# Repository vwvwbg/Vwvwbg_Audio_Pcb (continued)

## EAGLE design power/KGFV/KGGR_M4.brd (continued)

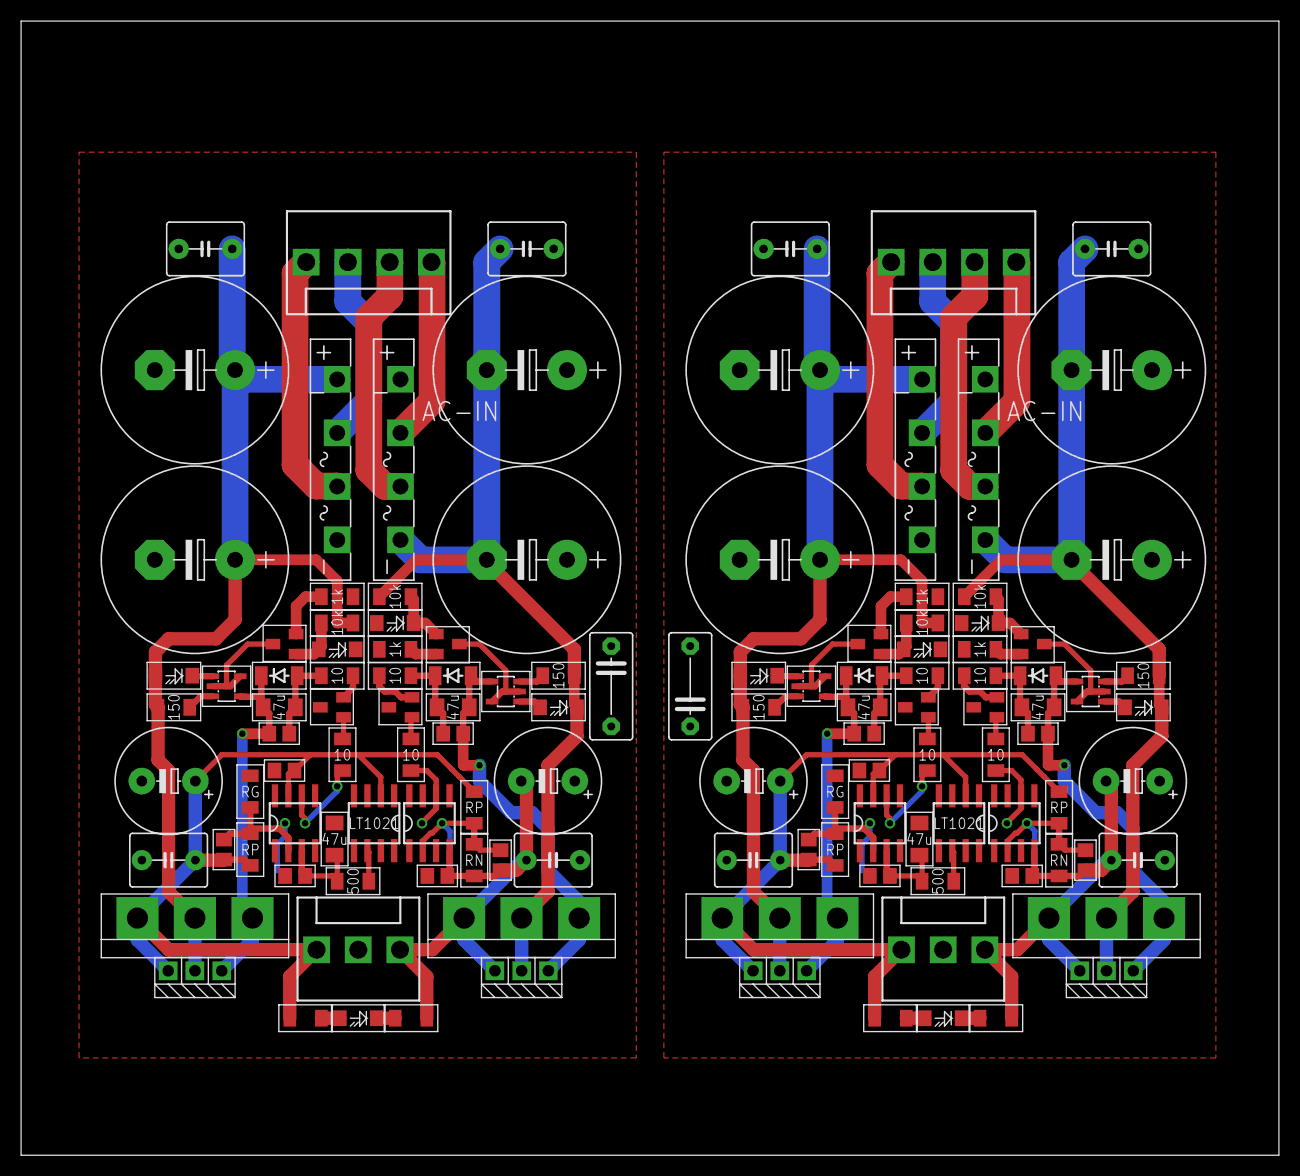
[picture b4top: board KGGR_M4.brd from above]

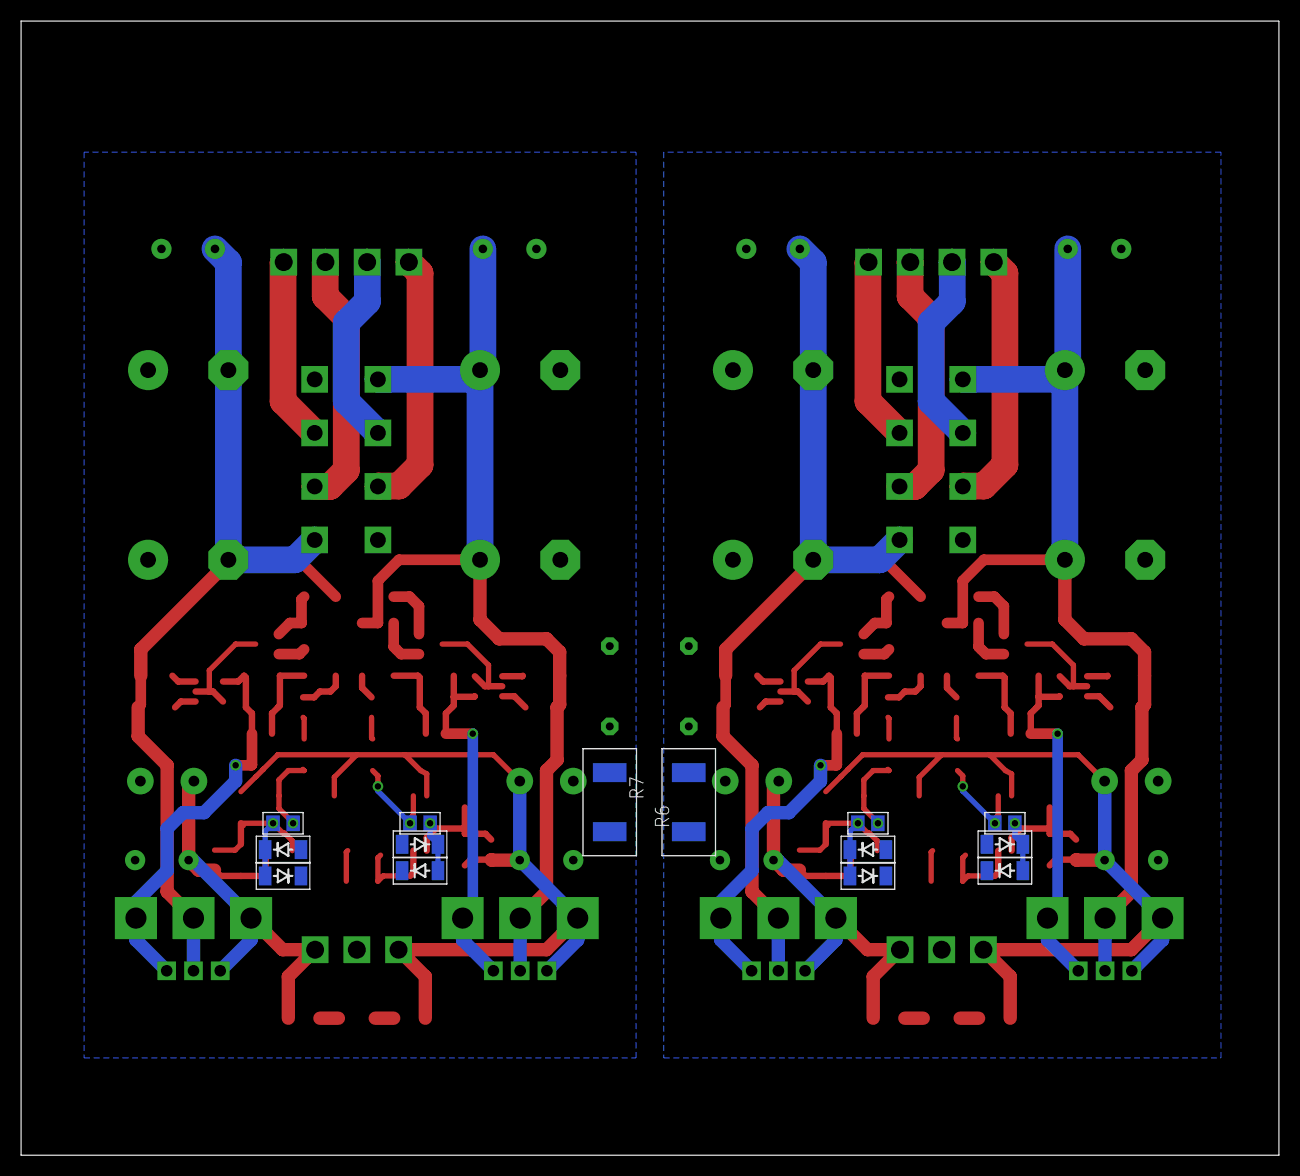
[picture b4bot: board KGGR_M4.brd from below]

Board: 2 copper layers, 119.4 x 107.6 mm, 138 parts (14 on the bottom side), 71 nets.
